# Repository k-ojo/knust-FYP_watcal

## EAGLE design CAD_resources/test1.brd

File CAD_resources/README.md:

# knust-FYP_watcal
this repo contains all files used in developing a gateway device for managing connection between a network energy meters in my FYP.

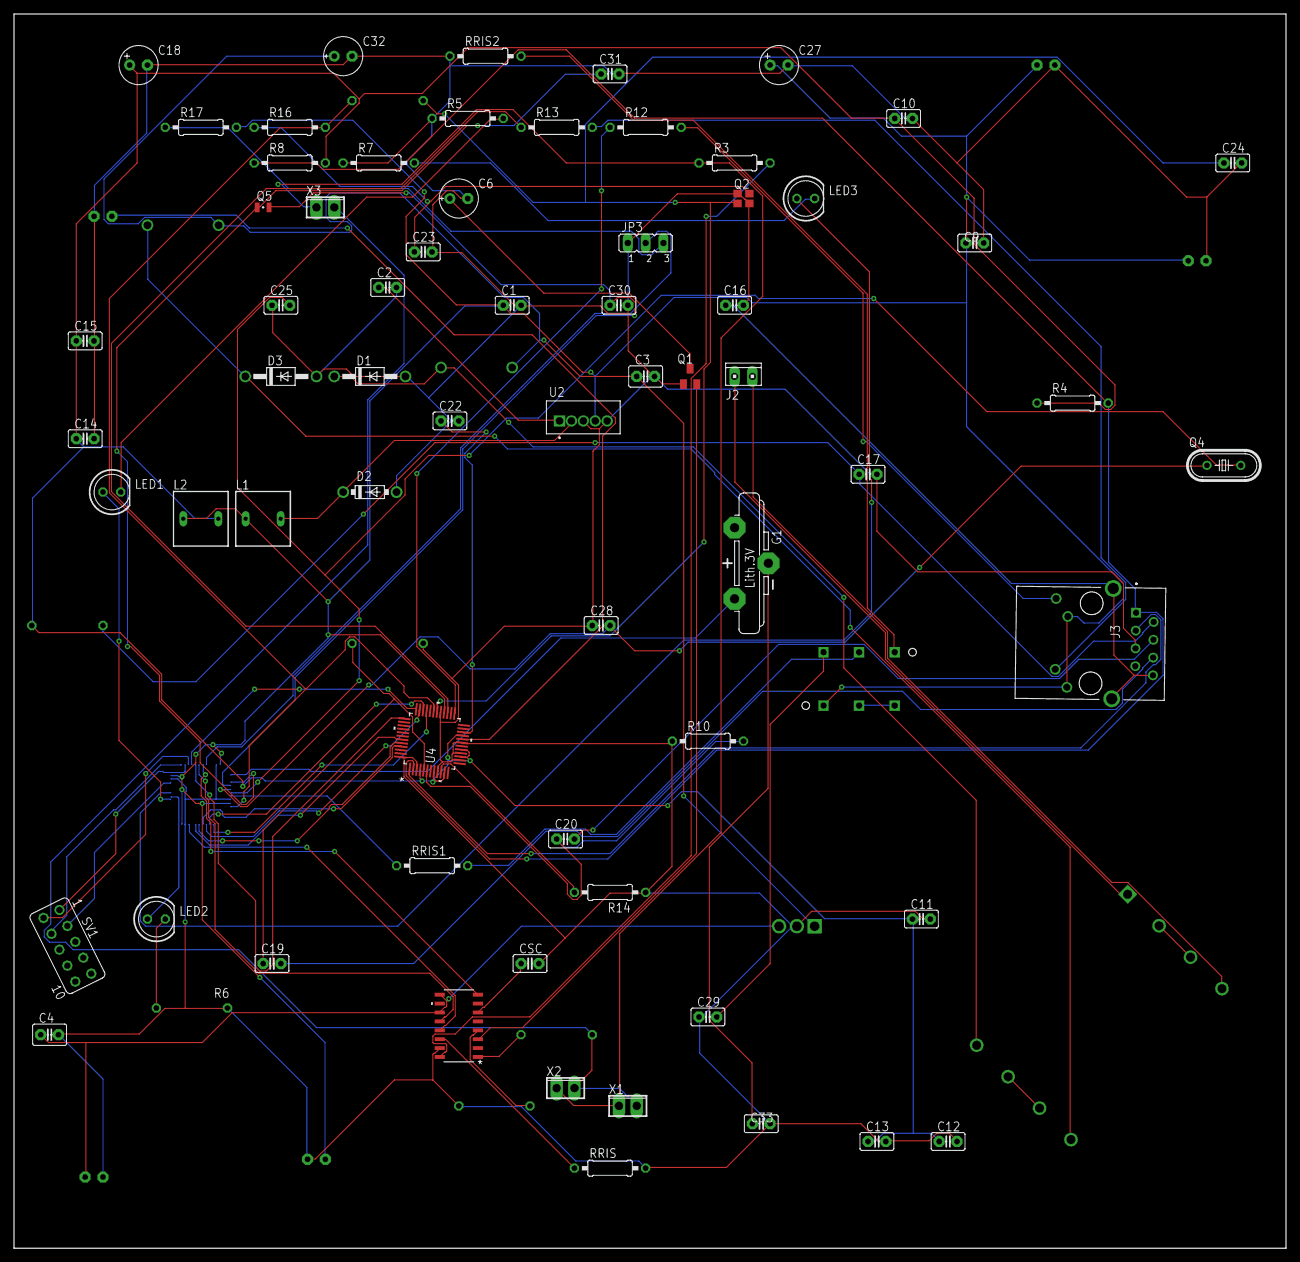
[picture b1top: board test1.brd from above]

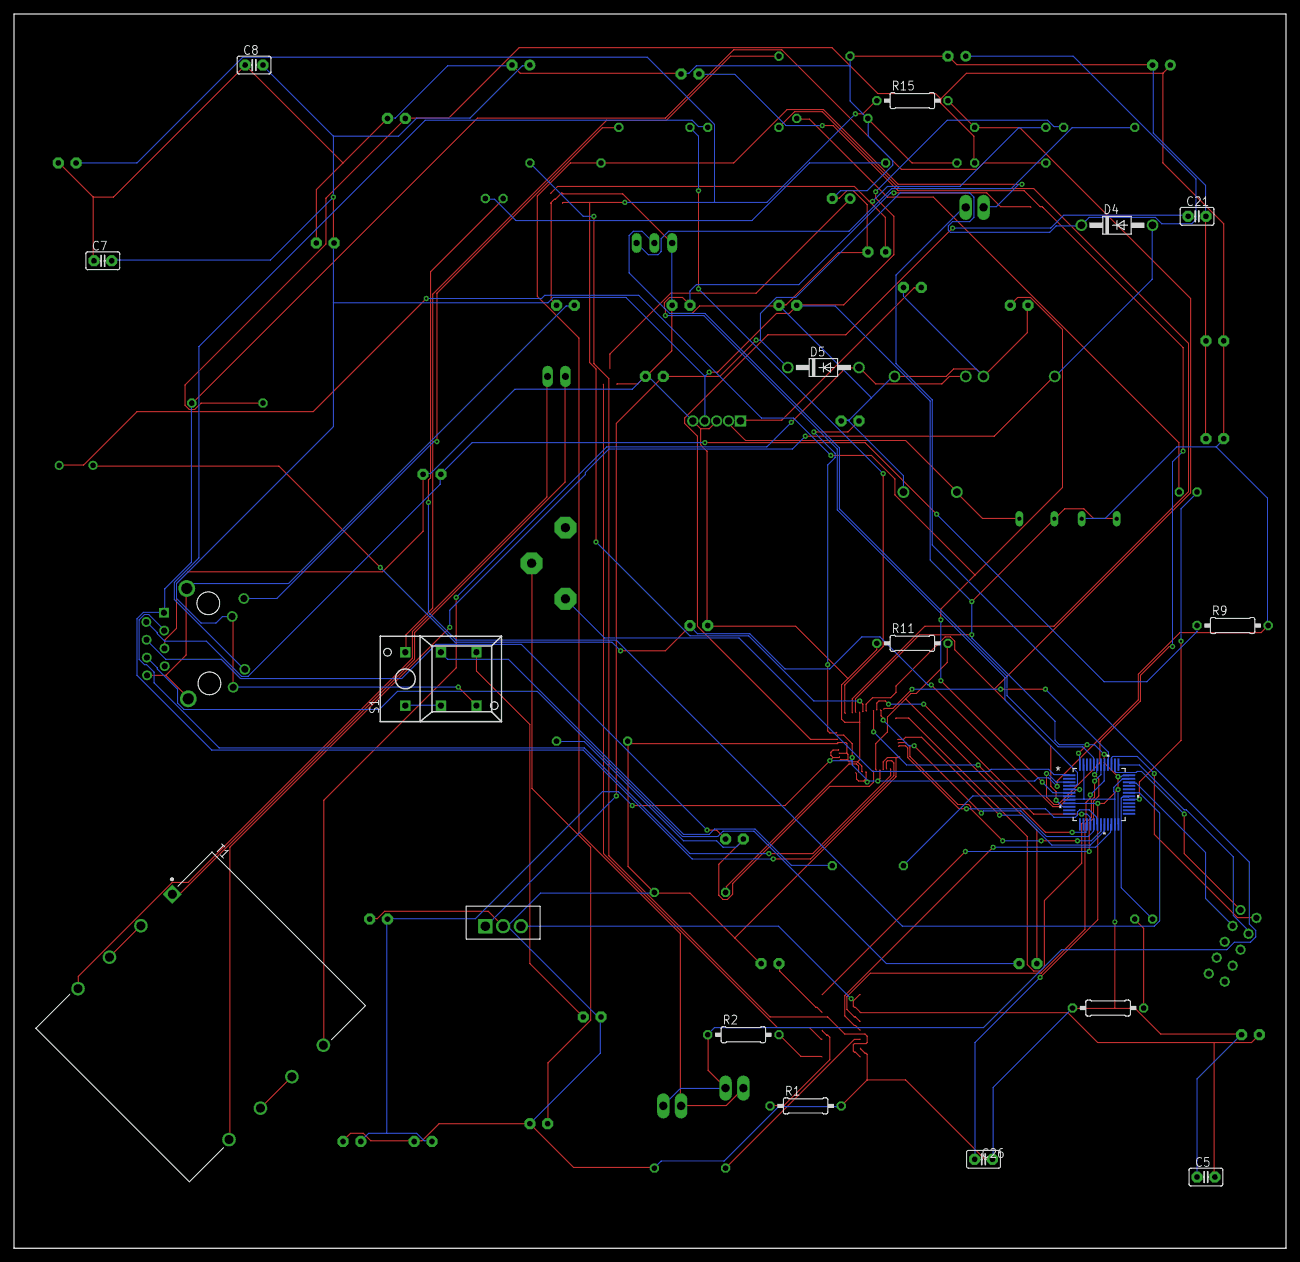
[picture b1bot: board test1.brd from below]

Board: 2 copper layers, 181.6 x 176.2 mm, 83 parts (17 on the bottom side), 74 nets.

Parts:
C1: 330uF; C2.5-2
C2: 100uF; C2.5-2
C3: 44uC; C2.5-3
C4: 22uC; C2.5-3
C5: 10uF; C2.5-2
C6: 300; E2,5-6E
C7, C8, C9, C10, C11, C12, C13, C15, C26: 0.1u; C2.5-2
C14: o.1u; C2.5-2
C16: 1nF/2kV; C2.5-2
C17, C19, C20: 22n; C2.5-2
C18, C27: 10u; E2,5-6
C21: 4.7uF; C2.5-2
C22: 10nF; C2.5-2
C23, C24: 18p; C2.5-2
C25, C28, C29: 12uF; C2.5-2
C30, C31: 12.5uF; C2.5-2
C32: 470uF; E2,5-6E
C33: 1u; C2.5-2
CSC: 10uF; C2.5-2
D1, D3, D4, D5: 1N4004; DO41-10
D2: 1N5819-B; DO41-7.6
G1: CR2032V
J2: 230V; 10X02MTA
J3: J1B1211CCD
JP3: JP2
L1, L2: SD8
LED1, LED2, LED3: LED5MM
Q1: BSS84; SOT23
Q2: 29MHz; FA-20H
Q4: HC49/S
Q5: 32.768; FC-12M
R1: 30k; 0207/10
R2, R3: 220; 0207/10
R4, R8, R9, R12, R13: 49.9 1%; 0207/10
R5, R6, R7: 0207/10
R10, R11: 49R9 1%; 0207/10
R14: 12.4k; 0207/10
R15: 1M; 0207/10
R16: 0R; 0207/10
R17: 10K; 0207/10
RRIS, RRIS1, RRIS2: 30k; 0207/10
S1: 5501-1LED
SV1: FE05-2
T1: 3FD-312; XFMR_3FD-312
U1: STM32F103C8T6LQFP48_STM-M; LQFP48_STM-M
U2: LM2576-3.3WT; TO170P1054X470X1514-5
U3: LM2940CT-5.0/NOPBT03B; T03B
U4: W550048LQFP_W5500_WIZ-M; 48LQFP_W5500_WIZ-M
U5: TSS721ADD16_TEX; D16_TEX
X1, X2, X3: 2POL254

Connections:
ACTLED: R12.1, U4.25
BUSL1: R3.1, X1.1, X2.1, X3.1
BUSL2: R2.1, X1.2, X2.2, X3.2
CGND: C16.1, J3.8, J3.13, J3.14
GND: C1.2, C2.2, C3.2, C4.2, C5.1, C6.-, C7.1, C8.1, C9.2, C10.2, C11.2, C12.2, C13.2, C14.2, C15.2, C16.2, C17.2, C18.-, C21.2, C22.2, C23.2, C24.2, C25.1, C26.2, C27.-, C28.1, C29.1, C30.2, C31.2, C32.-, C33.2, CSC.2, D1.A, D2.A, D3.A, J3.5, JP3.1, Q1.1, Q2.2, Q2.4, R1.2, R5.1, R6.1, R7.1, R10.1, R11.1, R14.1, RRIS.2, RRIS2.1, U1.8, U1.23, U1.35, U1.47, U2.3, U2.5, U3.2, U4.3, U4.9, U4.14, U4.16, U4.19, U4.29, U4.48, U5.15
INTN: U1.40, U4.36
JTCK: SV1.4, U1.37
JTDI: SV1.1, U1.38
JTDO: SV1.2, U1.39
JTMS: SV1.3, U1.34
LED1: LED1.A, U1.29
LED2: LED2.A, U1.30
LED3: LED3.A, U1.31
LINKLED: R13.1, U4.27
MISO: U1.16, U4.34
MOSI: U1.17, U4.35
unnamed: D2.C, L1.2, U2.2
unnamed: U1.42, U5.12
unnamed: CSC.1, U5.6
unnamed: Q1.2, U5.3
unnamed: C6.+, Q1.3
unnamed: LED1.K, R5.2
unnamed: LED2.K, R6.2
unnamed: LED3.K, R7.2
unnamed: J3.3, U4.1
unnamed: J3.1, R4.2, R8.1, U4.2
unnamed: C17.1, J3.2, R9.1
unnamed: C19.1, R11.2, U4.5
unnamed: C21.1, U4.20
unnamed: C20.1, R10.2, U4.6
unnamed: C20.2, J3.4
unnamed: C19.2, J3.6
unnamed: J3.11, R13.2
unnamed: J3.9, R12.2
unnamed: JP3.2, U1.44
unnamed: R14.2, U4.10
unnamed: C24.1, Q2.1, R15.1, U4.30
unnamed: C22.1, U4.22
unnamed: C25.2, Q4.2, U1.6
unnamed: C23.1, Q2.3, R16.1
unnamed: JP3.3, R17.1
unnamed: C28.2, Q4.1, U1.5
unnamed: C29.2, S1.NO
unnamed: RRIS1.2, S1.1A
unnamed: RRIS1.1, U1.7
unnamed: C31.1, Q5.1, U1.3
unnamed: C30.1, Q5.2, U1.4
unnamed: G1.+, U1.1
unnamed: C33.1, G1.-
unnamed: C2.1, U2.1
unnamed: S1.1B, S1.+
unnamed: RRIS2.2, S1.-
unnamed: T1.6, T1.7
unnamed: J2.2, T1.1
unnamed: T1.2, T1.3
unnamed: J2.1, T1.4
unnamed: D1.C, D5.A, T1.5
unnamed: D3.C, D4.A, T1.8
PB7: U1.43, U5.8
PMODE0: U1.18, U4.45
PMODE1: U1.19, U4.44
PMODE2: U1.20, U4.43
RIDD: R1.1, U5.4
RIS: RRIS.1, U5.14
RL1: R3.2, U5.16
RL2: R2.2, U5.1
RSTN: U1.41, U4.37
RXI: U1.22, U5.13
SCLK: U1.15, U4.33
SCSN: R15.2, R16.2, U1.10, U4.31
V3.3: C1.1, C7.2, C8.2, C9.1, C26.1, C27.+, J3.10, J3.12, L1.1, L2.1, R17.2, S1.NC, U1.9, U1.24, U1.36, U1.48, U2.4, U4.28
V3.3A: C10.1, C11.1, C12.1, C13.1, C14.1, C15.1, C18.+, L2.2, R4.1, R8.2, R9.2, U4.4, U4.8, U4.11, U4.15, U4.17, U4.21
V5.0: C4.1, C5.2, U3.3, U5.9, U5.11
VIN: C3.1, C32.+, D4.C, D5.C, U3.1

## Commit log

2024-06-06 components
2024-06-21 added cad resources
2024-06-21 added more files
2024-06-22 test file
2024-06-22 Updated test
2024-06-22 Tired
2024-06-22 added gebber files
2024-06-22 added gebber
2024-06-24 added bom
2024-06-25 Test
2024-07-02 the init file
2024-07-02 added public
2024-07-02 cleaned up
2024-07-02 added meters
2024-07-02 Create master
2024-07-02 added master.c
2024-07-02 added slave
2024-07-03 added essentials 4
2024-07-03 modified master.c
2024-07-03 added include
2024-07-03 added helper
2024-07-03 added src
2024-07-03 added some files
2024-07-03 added some files for testing
2024-07-03 adde file
2024-07-03 added files
2024-07-03 Rename slave.c to master.c
2024-07-04 added abstract
2024-07-05 cleaned
2024-07-05 added
2024-07-07 added some changes to slave.c
2024-07-07 modified master and slave
2024-07-07 modied some files and added new
2024-07-12 added new to watcal

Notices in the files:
parts and their libraries:
COPYRIGHT: Copyright (C) 2024 Ultra Librarian. All rights reserved.
